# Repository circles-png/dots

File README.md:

dots
=======

Rust project for the _Arduino Uno_.

## Build Instructions
1. Install prerequisites as described in the [`avr-hal` README] (`avr-gcc`, `avr-libc`, `avrdude`, [`ravedude`]).

2. Run `cargo build` to build the firmware.

3. Run `cargo run` to flash the firmware to a connected board.  If `ravedude`
   fails to detect your board, check its documentation at
   <https://crates.io/crates/ravedude>.

4. `ravedude` will open a console session after flashing where you can interact
   with the UART console of your board.

[`avr-hal` README]: https://github.com/Rahix/avr-hal#readme
[`ravedude`]: https://crates.io/crates/ravedude

## License
Licensed under either of

 - Apache License, Version 2.0
   ([LICENSE-APACHE](LICENSE-APACHE) or <http://www.apache.org/licenses/LICENSE-2.0>)
 - MIT license
   ([LICENSE-MIT](LICENSE-MIT) or <http://opensource.org/licenses/MIT>)

at your option.

## Contribution
Unless you explicitly state otherwise, any contribution intentionally submitted
for inclusion in the work by you, as defined in the Apache-2.0 license, shall
be dual licensed as above, without any additional terms or conditions.

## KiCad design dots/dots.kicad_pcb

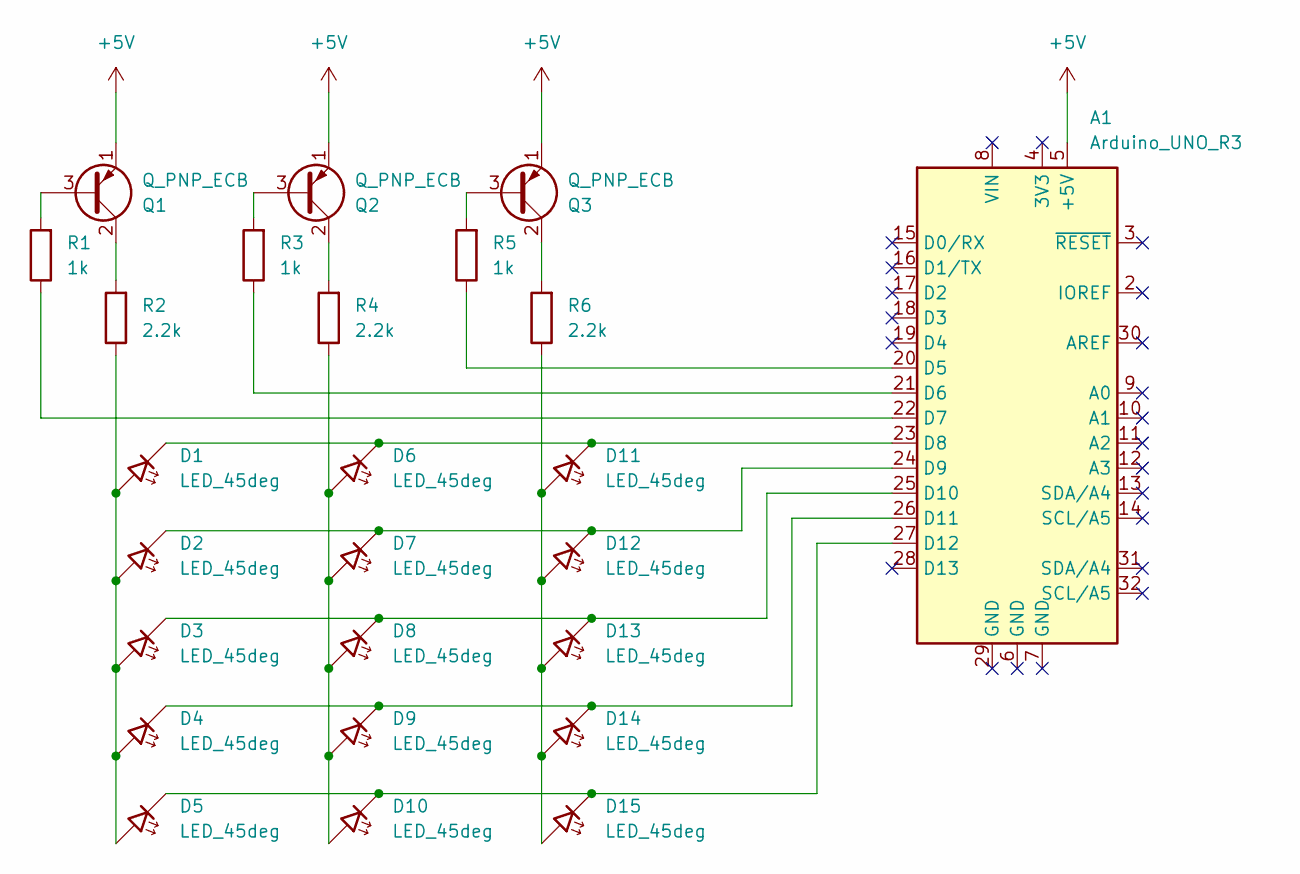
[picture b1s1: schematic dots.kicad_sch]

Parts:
A1: Arduino_UNO_R3
D1, D2, D3, D4, D5, D6, D7, D8, D9, D10, D11, D12, D13, D14, D15: LED_45deg; LED_D3.0mm
Q1, Q2, Q3: Q_PNP_ECB; TO-92_Inline
R1, R3, R5: 1k; R_Axial_DIN0207_L6.3mm_D2.5mm_P7.62mm_Horizontal
R2, R4, R6: 2.2k; R_Axial_DIN0207_L6.3mm_D2.5mm_P7.62mm_Horizontal

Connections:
+5V: A1.5 (+5V), Q1.1 (E), Q2.1 (E), Q3.1 (E)
unnamed: A1.20 (D5), R5.1
unnamed: A1.21 (D6), R3.1
unnamed: A1.22 (D7), R1.1
unnamed: A1.23 (D8), D1.1 (K), D6.1 (K), D11.1 (K)
unnamed: A1.24 (D9), D2.1 (K), D7.1 (K), D12.1 (K)
unnamed: A1.25 (D10), D3.1 (K), D8.1 (K), D13.1 (K)
unnamed: A1.26 (D11), D4.1 (K), D9.1 (K), D14.1 (K)
unnamed: A1.27 (D12), D5.1 (K), D10.1 (K), D15.1 (K)
unnamed: D1.2 (A), D2.2 (A), D3.2 (A), D4.2 (A), D5.2 (A), R2.1
unnamed: D6.2 (A), D7.2 (A), D8.2 (A), D9.2 (A), D10.2 (A), R4.1
unnamed: D11.2 (A), D12.2 (A), D13.2 (A), D14.2 (A), D15.2 (A), R6.1
unnamed: Q1.3 (B), R1.2
unnamed: Q1.2 (C), R2.2
unnamed: Q2.3 (B), R3.2
unnamed: Q2.2 (C), R4.2
unnamed: Q3.3 (B), R5.2
unnamed: Q3.2 (C), R6.2

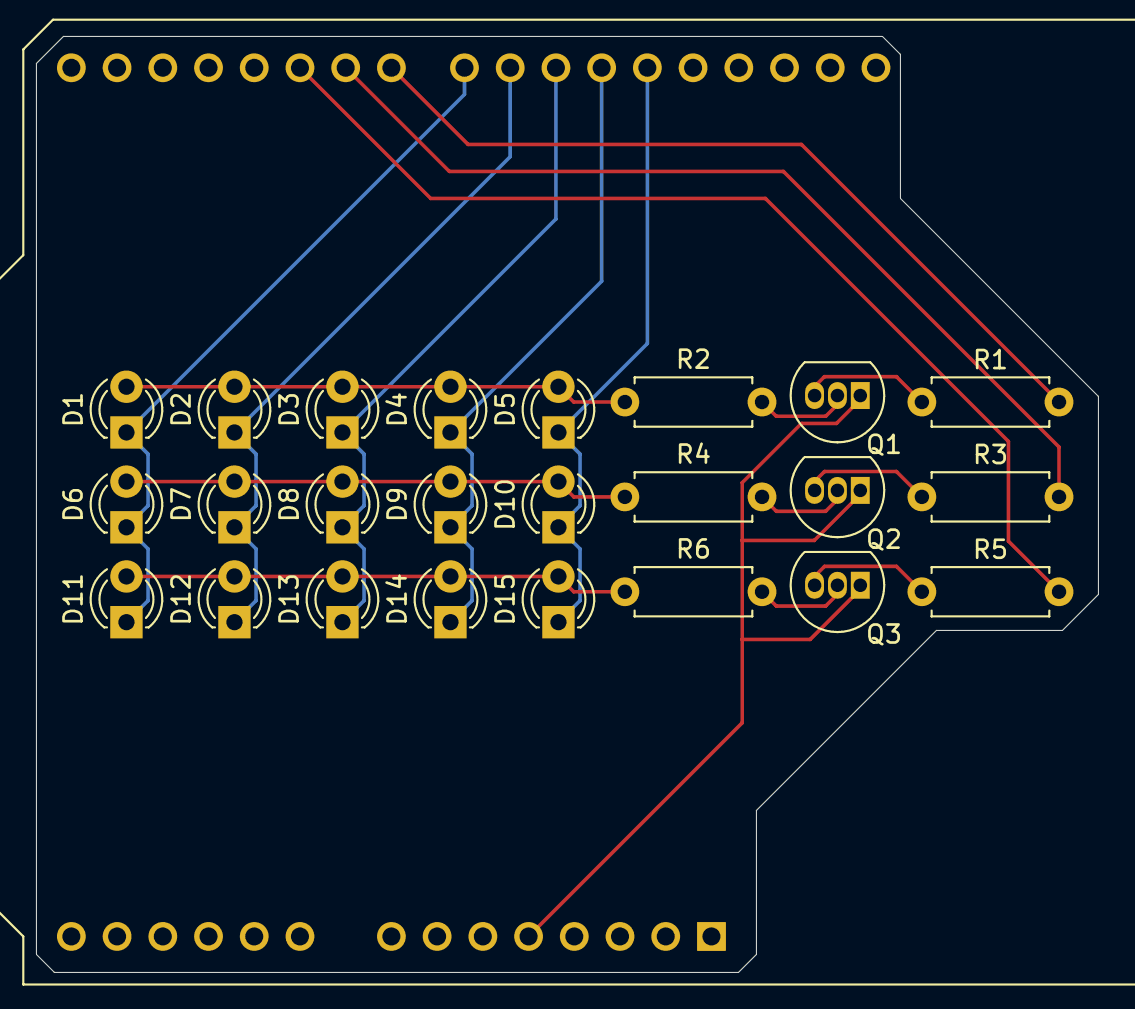
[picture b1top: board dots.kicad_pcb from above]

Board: 2 copper layers, 59.0 x 52.0 mm, 25 parts (0 on the bottom side), 18 nets.

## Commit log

2024-07-09 Add AVR target configurations for various microcontrollers
2024-07-09 Add .DS_Store, dots/dots-backups, and fp-info-cache to .gitignore Add dots/dots.kicad_prl file with board and git configurations
